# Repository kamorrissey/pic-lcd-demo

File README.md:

# pic-lcd-demo

Demonstration of driving a multiplexed LCD segment display using the LCD driver module of a PIC16LF19156 MCU.
Includes two versions of another PIC-based circuit, a poor person's AC square wave generator to use to test an LCD segment display.

# Contents

There are two circuits with firmware in this project:
* a [demonstration of driving an LCD segment display](LCD_Demo.md) with a PIC16LF19156 MCU, which has a built-in LCD driver module
* three versions of an [AC square wave generator](LCD_Test_Generator.md) adequate for testing a bare LCD
  * one using the same PICLF19156 MCU
  * one using a smaller, cheaper PIC12F1572 MCU that generates the square wave using software
  * one using a PIC12F1572 MCU that generates the square wave using built-in pulse width modulation (PWM) circuitry
  
Both PIC12F1572 versions run on the same circuit, just with different firmware.

There are two directories at this level:
* [kicad](kicad) - KiCad projects for schematics
* [mplabx](mplabx) - MPLAB X IDE projects for PIC microcontroller firmware, written in C

# Introduction

In 2020, I helped a non-profit design a non-contact IR fever thermometer,
the kind where you point it at a forehead and press a button or pull a trigger to take a temperature.
At the time, the non-profit expected there would become a shortage of these thermometers.
Several design proposals were submitted, including by me.

My proposal, which was not selected, had two characteristics making it different from the others.
I specified a Microchip PIC MCU and an LCD display; the others specified Arduino-compatible MCUs and LED displays.
I picked an LCD for low power consumption and high visibility in normal to bright lighting, such as at a well-lit business or even sunlight.
I selected a model of PIC that had a built-in LCD driver module.

In the aftermath of the thermometer effort,
I decided to build a working prototype of my design,
and this project was a stepping stone to getting there.
I decided to document this stepping stone
because I could find precious little on the internet
about programming the Microchip PIC built-in LCD driver module.

LCD displays are much more complicated to drive than LED displays,
because LCDs are driven by AC signals only.
LCDs are damaged if a long-term DC bias is applied to them.
Microchip simplifies LCD circuit design by building into some of their PIC MCU models
LCD driver circuits that produce suitable AC waveforms.
The PIC LCD module in some PICs also provides a regulated charge pump that can be used for LCD bias,
but that will not be demonstrated here.
The regulated charge pump is both step-up and step-down.

This project demonstrates a minimal circuit and firmware
driving a 3V, multiplexed, 12-pin, LCD segment display (Lumex LCD-S401M16KR)
with a 28-pin DIP Microchip PIC16LF19156 MCU operating at about 3V.

There are two separate but related circuits in the project:
1. Two versions of a circuit and firmware for a poor-person's 3V AC square wave generator to use for testing bare LCD displays
2. A circuit and firmware to show something on the LCD display

# About the Hardware

Schematics and KiCad projects for all circuits are provided.
KiCad is a FOSS design tool for circuits and printed circuit boards.

All the circuits in this project can be easily breadboarded.

## Microcontroller

I chose a PICLF19156-I/SP MCU
([datasheet](https://ww1.microchip.com/downloads/en/DeviceDoc/PIC16LF19155-56-75-76-85-86-Data-Sheet-40001923B.pdf))
for my non-contact thermometer design for several reasons:
* 28-pin SPDIP package is breadboardable and hand solderable
* lowest adequate pin count and footprint of a PIC that has a built-in LCD driver module
* able to directly operate off 3V provided by 2xAA cells or 1xAA cell with a boost converter
* has I2C/IIC/SMBus interface for eventually communicating with a Melexis MLX90614 IR temperature sensor

It is both narrower and smaller than the 40-pin DIP PIC16F19176
([datasheet](https://ww1.microchip.com/downloads/en/DeviceDoc/PIC16LF19155-56-75-76-85-86-Data-Sheet-40001923B.pdf))
that I originally considered.
The LF chips are also lower-power than the F chips,
operating at 1.8V-3.6V, compared to 2.4V-5.5V for the F chips.
You can also use to PIC16F19156 (note the F instead of LF)
to have the flexibility to operate at 3V or 5V.
The PIC(L)F19175/6
([datasheet](https://ww1.microchip.com/downloads/en/DeviceDoc/PIC16LF19155-56-75-76-85-86-Data-Sheet-40001923B.pdf))
would work with minor changes to circuits and firmware.
If you use a different LCD, it may be static (unmultiplexed);
if so, you may need to use a surface mount PIC with more pins,
such as PIC16(L)F19185/6 (44-pin) or PIC16(L)F19195/6/7 (64-pin).

The hardware design is as minimal as I could make it.
The PIC's internal oscillators are used, eliminating the need for external crystals.
The design is low-power, with the optional LED being the biggest current draw.
There are enough spare pins on the PIC16(L)F19156 for a couple of switches and an I2C/IIC/SMBus interface, which were needed in the thermometer project.

The circuits include a 5-pin header for programming in-circuit with a PIC ICSP programmer.
I used a [Pickit 4](https://www.microchip.com/developmenttools/ProductDetails/PG164140) programmer/debugger;
there may be cheaper alternatives, such as the older
[PicKit 3](https://www.amazon.com/Microchip-Programmer-Debugger-Emulator-Controller/dp/B07WS5JL3Z).

I also implemented the square wave generator using
an 8-pin, very inexpensive ($0.80 quantity one) PIC12F1572-I/P
([datasheet](https://ww1.microchip.com/downloads/en/DeviceDoc/40001723D.pdf)),
which will operate at 2.4V-5.5V,
making it suitable for testing either 3V or 5V LCDs.
That circuit and firmware are also provided.

## LCD Display

LCD displays require much less current to operate (microamps)
than LED displays (milliamps).

The display I chose for the my thermometer project was a Lumex LCD-S401M16KR
([datasheet](https://www.lumex.com/datasheet/LCD-S401M16KR))
available cheaply (<$2 quantity 1) from Digikey and Mouser.
It is a 4-digit, 7-segment display
with 3 decimal points and a colon
operating at 3VAC.
It is 4-way multiplexed,
allowing a 28- or 40-pin MCU to be adequate since only 12 pins
(4 common, 8 segment)
are needed to drive the 32 (4*8 = 32) pixels of the display.
This is the LCD that will be used here.

Similar static (unmultiplexed) displays would likely require an SMT MCU
such as the PIC16(L)F19185/6 (44-pin) or PIC16(L)F19195/6/7 (64-pin).

The lead pitch of the LCD is small, only 1.5mm.
I believe the long leads can be spread wide enough to plug into a breadboard,
but I had difficulty doing so and instead ordered a short run of [the only breakout board I could find compatible with this device](https://oshpark.com/shared_projects/sJmRuwZJ).

# About the Firmware 

The firmware for all circuits is in C, using the free Microchip MPLAB X IDE and XC8 compiler.
I flashed my software using the Microchip PicKit 4 programmer and debugger.
There may be cheaper alternatives,
but I'm still too new to PICs to recommend anything other than the PicKit 4
(or PicKit 3, which is older and cheaper).

The full MPLAB X projects for the firmware are provided.

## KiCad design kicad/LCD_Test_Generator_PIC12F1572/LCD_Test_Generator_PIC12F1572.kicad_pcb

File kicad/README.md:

# KiCad Circuits

KiCad ([kicad.org](https://www.kicad.org/)) is a FOSS application for designing circuits and printed circuit boards.
It was used to create the circuit schematics for this project.

There are three KiCad circuit projects in this directory:
* [LCD_Test_Generator](LCD_Test_Generator), a 250Hz AC square wave generator for testing bare LCD displays using a PICLF19156 MCU
* [LCD_Test_Generator_PIC12F1572](LCD_Test_Generator_PIC12F1572), the same generator, but using a smaller, cheaper PIC12F1572 MCU
* [LCD_Demo](LCD_Demo), a demonstration of driving an LCD from a PICLF19156 MCU

To open any of these KiCad circuit projects, open in KiCad the \*.pro file
in the respective directory.

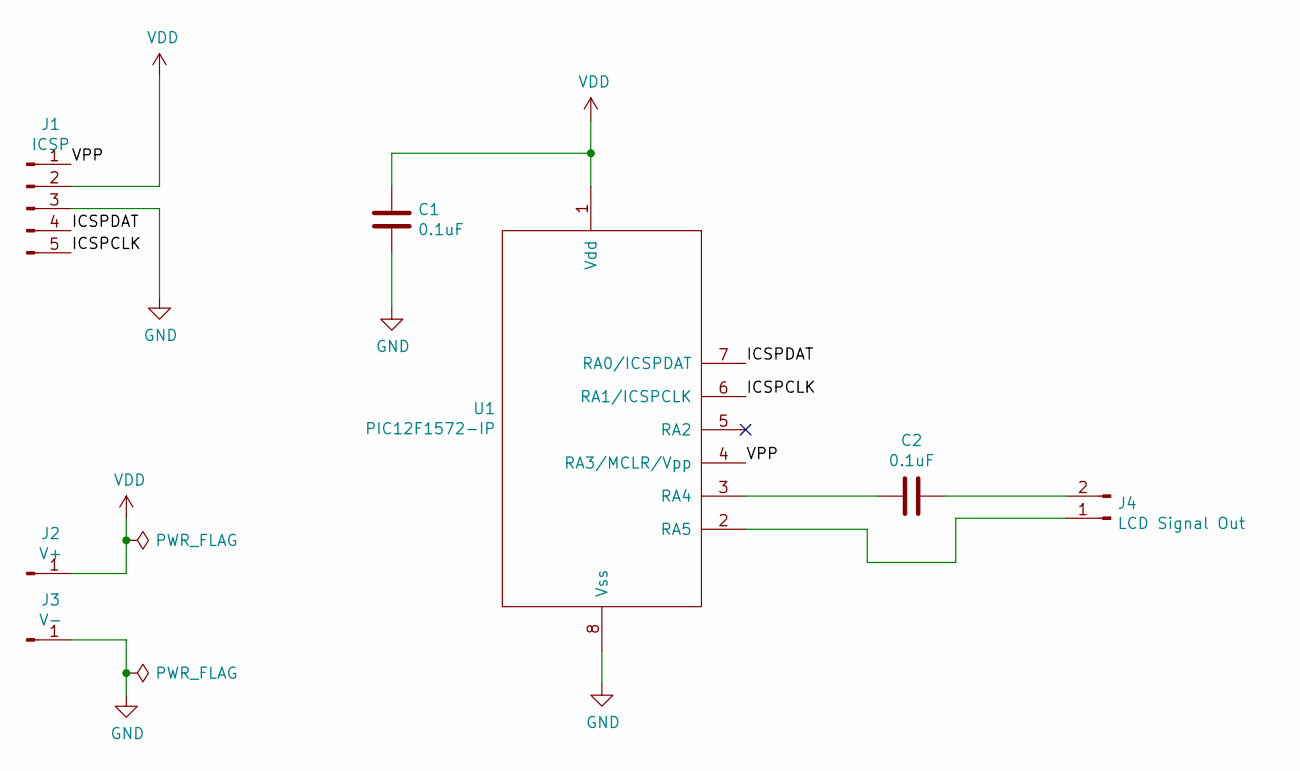
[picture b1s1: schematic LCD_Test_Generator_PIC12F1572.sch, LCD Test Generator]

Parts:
C1, C2: 0.1uF; C_Disc_D3.0mm_W1.6mm_P2.50mm
J1: ICSP; PinHeader_1x05_P2.54mm_Horizontal
J2: V+; PinHeader_1x01_P2.54mm_Vertical
J3: V-; PinHeader_1x01_P2.54mm_Vertical
J4: LCD Signal Out; PinHeader_1x02_P2.54mm_Vertical
U1: PIC12F1572-IP; DIP-8_W7.62mm_Socket

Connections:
/ICSPCLK: J1.5, U1.6 (RA1/ICSPCLK)
/ICSPDAT: J1.4, U1.7 (RA0/ICSPDAT)
/VPP: J1.1, U1.4 (RA3/MCLR/Vpp)
GND: C1.1, J1.3, J3.1, U1.8 (Vss)
unnamed: C2.1, J4.2
unnamed: C2.2, U1.3 (RA4)
unnamed: J4.1, U1.2 (RA5)
VDD: C1.2, J1.2, J2.1, U1.1 (Vdd)

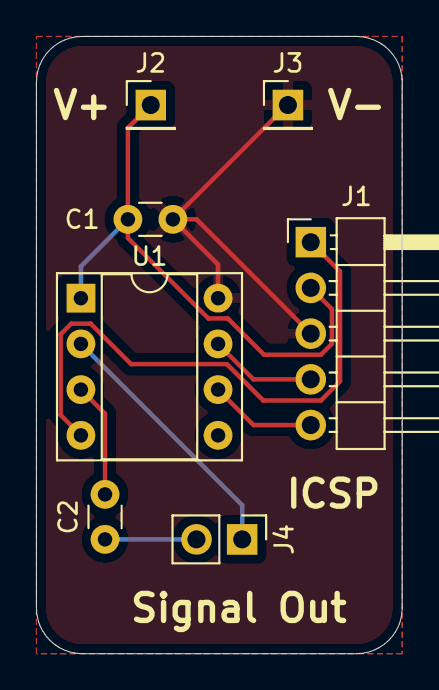
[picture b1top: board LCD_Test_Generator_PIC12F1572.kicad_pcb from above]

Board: 2 copper layers, 20.3 x 34.3 mm, 7 parts (0 on the bottom side), 8 nets.

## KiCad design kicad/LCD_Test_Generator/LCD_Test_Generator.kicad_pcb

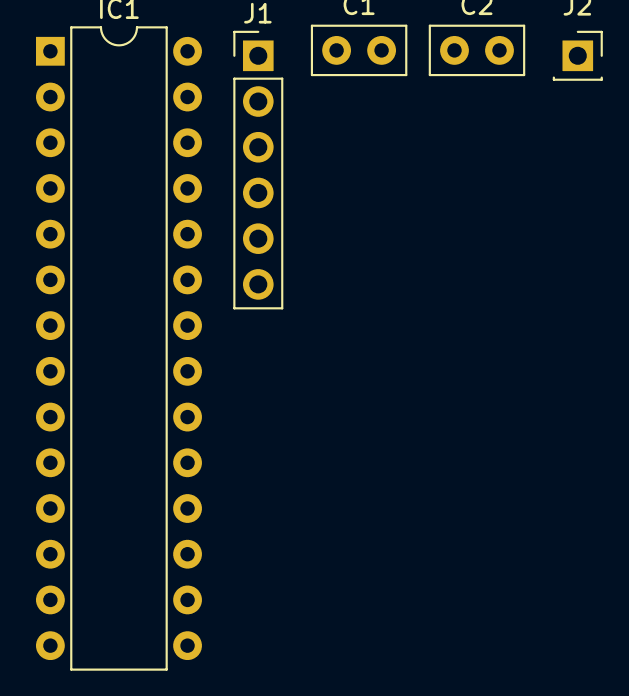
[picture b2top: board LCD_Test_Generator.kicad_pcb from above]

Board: 2 copper layers, 5 parts (0 on the bottom side), 7 nets, no tracks yet.

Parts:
C1, C2: 100nF; C_Disc_D5.0mm_W2.5mm_P2.50mm
IC1: PIC16LF19156-I_SP; DIP-28_W7.62mm
J1: ICSP; PinHeader_1x06_P2.54mm_Vertical
J2: LCD Signal Output; PinSocket_1x01_P2.54mm_Vertical

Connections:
+3V0: C2.1, IC1.20, J1.2
/ICSP_CLK: IC1.27, J1.5
/ICSP_DAT: IC1.28, J1.4
/ICSP_VPP: IC1.1, J1.1
GND: C2.2, IC1.8, IC1.19, J1.3
unnamed: C1.1, IC1.11
unnamed: C1.2, J2.1

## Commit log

2021-04-26 Add schematic at top level
2021-04-30 First check-in of kicad and mplab projects
2021-04-30 Add LCD_Test_Generator_Schematic.pdf
2021-05-01 update mplab for LVP
2021-05-01 Set theme jekyll-theme-slate
2021-05-28 README changes, make LCD work, add PIC12F1572 test generator
2021-05-28 Expanded READMEs
2021-05-28 Update README.md
    Fix README.md
2021-05-28 Update README.md
    Add main image to README.md
2021-05-28 Rough in README.md files for MPLAB projects
2021-05-28 Improvements to all code projects
2021-05-28 Add LC Demo README.md
2021-05-28 Update BOM
2021-05-28 Switch LCD to low-power internal ladder
2021-06-17 Update mplab x toolchain
2021-06-20 Add test generator using PWM modules
2022-02-10 Implement LCD tester using PWM
